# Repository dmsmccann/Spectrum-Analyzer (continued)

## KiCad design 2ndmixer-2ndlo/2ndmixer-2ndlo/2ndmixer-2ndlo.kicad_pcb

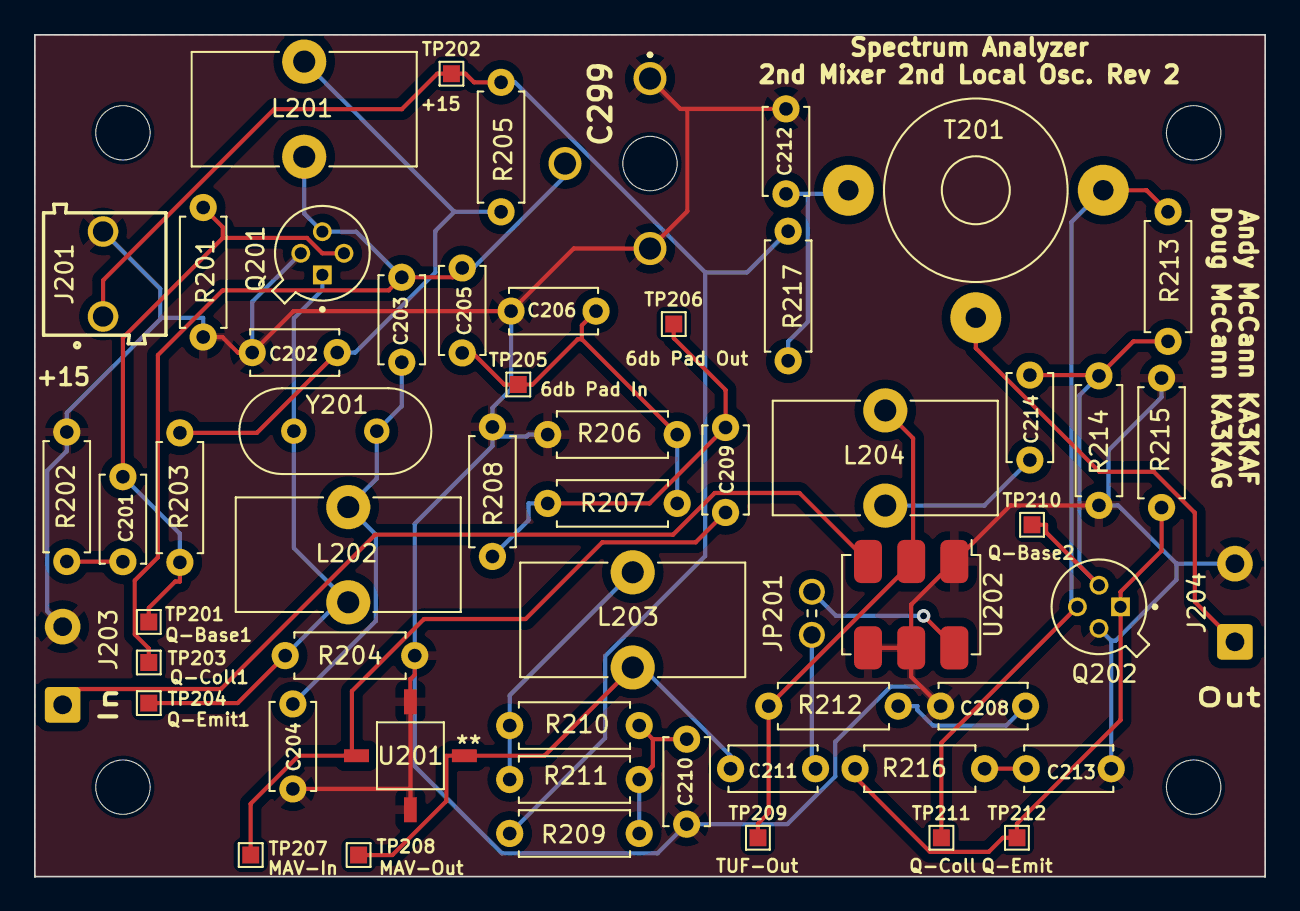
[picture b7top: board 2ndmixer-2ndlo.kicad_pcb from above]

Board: 2 copper layers, 72.4 x 49.5 mm, 61 parts (0 on the bottom side), 26 nets.

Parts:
C201, C202: 470p; C_Disc_D5.0mm_W2.5mm_P5.00mm
C203, C204: 33p; C_Disc_D5.0mm_W2.5mm_P5.00mm
C205: 15p; C_Disc_D5.0mm_W2.5mm_P5.00mm
C206: 82p; C_Disc_D5.0mm_W2.5mm_P5.00mm
C208: 120p; C_Disc_D5.0mm_W2.5mm_P5.00mm
C209, C210, C211: .01u; C_Disc_D5.0mm_W2.5mm_P5.00mm
C212, C213, C214: .1u; C_Disc_D5.0mm_W2.5mm_P5.00mm
C299: 12p-60p; BFC280831659
H201, H202, H203, H204: MountingHole; MountingHole_3.2mm_M3
J201: Conn_01x02; 691103110002
J203: 110 MHz In; SolderWire-0.5sqmm_1x02_P4.6mm_D0.9mm_OD2.1mm
J204: 2nd IF Out; SolderWire-0.5sqmm_1x02_P4.6mm_D0.9mm_OD2.1mm
JP201: 5025; KEYSTONE_5025
L201: 40n; L_Toroid_Vertical_L13.0mm_W6.5mm_P5.60mm
L202: 420n; L_Toroid_Vertical_L13.0mm_W6.5mm_P5.60mm
L203, L204: 1u; L_Toroid_Vertical_L13.0mm_W6.5mm_P5.60mm
Q201, Q202: 2N5179; TO127P584H533-4N
R201, R213: 2k; R_Axial_DIN0207_L6.3mm_D2.5mm_P7.62mm_Horizontal
R202: 39; R_Axial_DIN0207_L6.3mm_D2.5mm_P7.62mm_Horizontal
R203: 3.3k; R_Axial_DIN0207_L6.3mm_D2.5mm_P7.62mm_Horizontal
R204: 510; R_Axial_DIN0207_L6.3mm_D2.5mm_P7.62mm_Horizontal
R205: 100; R_Axial_DIN0207_L6.3mm_D2.5mm_P7.62mm_Horizontal
R206, R208: 150; R_Axial_DIN0207_L6.3mm_D2.5mm_P7.62mm_Horizontal
R207: 36; R_Axial_DIN0207_L6.3mm_D2.5mm_P7.62mm_Horizontal
R209: 47; R_Axial_DIN0207_L6.3mm_D2.5mm_P7.62mm_Horizontal
R210, R211: 220; R_Axial_DIN0207_L6.3mm_D2.5mm_P7.62mm_Horizontal
R212: 51; R_Axial_DIN0207_L6.3mm_D2.5mm_P7.62mm_Horizontal
R214: 390; R_Axial_DIN0207_L6.3mm_D2.5mm_P7.62mm_Horizontal
R215, R217: 27; R_Axial_DIN0207_L6.3mm_D2.5mm_P7.62mm_Horizontal
R216: 5.1; R_Axial_DIN0207_L6.3mm_D2.5mm_P7.62mm_Horizontal
T201: Bifilar_Transformer; Autotransformer_Toroid_1Tap_Horizontal_D10.5mm_Amidon-T37
TP201: Q-Base1; TestPoint_Pad_1.0x1.0mm
TP202: +15; TestPoint_Pad_1.0x1.0mm
TP203: Q-Coll1; TestPoint_Pad_1.0x1.0mm
TP204: Q-Emit1; TestPoint_Pad_1.0x1.0mm
TP205: 6db Pad In; TestPoint_Pad_1.0x1.0mm
TP206: 6db Pad Out; TestPoint_Pad_1.0x1.0mm
TP207: MAV-In; TestPoint_Pad_1.0x1.0mm
TP208: MAV-Out; TestPoint_Pad_1.0x1.0mm
TP209: ADE-Out; TestPoint_Pad_1.0x1.0mm
TP210: Q-Base2; TestPoint_Pad_1.0x1.0mm
TP211: Q-Coll2; TestPoint_Pad_1.0x1.0mm
TP212: Q-Emit2; TestPoint_Pad_1.0x1.0mm
U201: MAV-11; MAV-11BSM&plus_
U202: ADE-1HW+; Mini-Circuits_CD636_H4.11mm
Y201: 100MHz; Crystal_HC49-U_Vertical

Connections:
/+15: J201.1, R205.1, R209.1, R217.1, TP202.1
GND: C202.2, C204.2, C206.2, C208.2, C210.2, C212.1, C213.1, C299.1 (R_1), C299.3 (R_2), J201.2, J203.2 (Ext), J204.2 (Ext), Q201.4 (SHIELD), Q202.4 (SHIELD), R201.2, R202.2, R204.2, R206.2, R208.2, R214.2, R215.2, U201.2 (GND), U201.4 (GND), U202.1 (GND), U202.4 (GND), U202.5 (GND)
unnamed: C201.1, Q201.2, R201.1, R203.2, TP201.1
unnamed: C201.2, R202.1
unnamed: C202.1, L201.1, R203.1, R205.2
unnamed: C203.2, C204.1, L202.1, Y201.2
unnamed: C205.2, C206.1, R206.1, R207.1, TP205.1
unnamed: C208.1, R212.2
unnamed: C209.1, R207.2, R208.1, TP206.1
unnamed: C210.1, R209.2, R210.1, R211.1
unnamed: C211.2, JP201.1
unnamed: C212.2, R217.2, T201.1
unnamed: C213.2, R216.2
unnamed: C214.1, L204.2
unnamed: C214.2, Q202.2, R213.2, R214.1, TP210.1
unnamed: C203.1, C205.1, C299.2 (S), L201.2, Q201.3, TP203.1
unnamed: J203.1 (In), U202.3 (RF)
unnamed: J204.1 (In), T201.2
unnamed: L202.2, Q201.1, R204.1, TP204.1, Y201.1
unnamed: L203.1, R210.2, R211.2
unnamed: Q202.1, R215.1, R216.1, TP212.1
unnamed: Q202.3, R213.1, T201.3, TP211.1
unnamed: C209.2, TP207.1, U201.1 (RF_In)
unnamed: C211.1, L203.2, TP208.1, U201.3 (RF_Out)
unnamed: L204.1, R212.1, TP209.1, U202.2 (IF)
unnamed: JP201.2, U202.6 (LO)

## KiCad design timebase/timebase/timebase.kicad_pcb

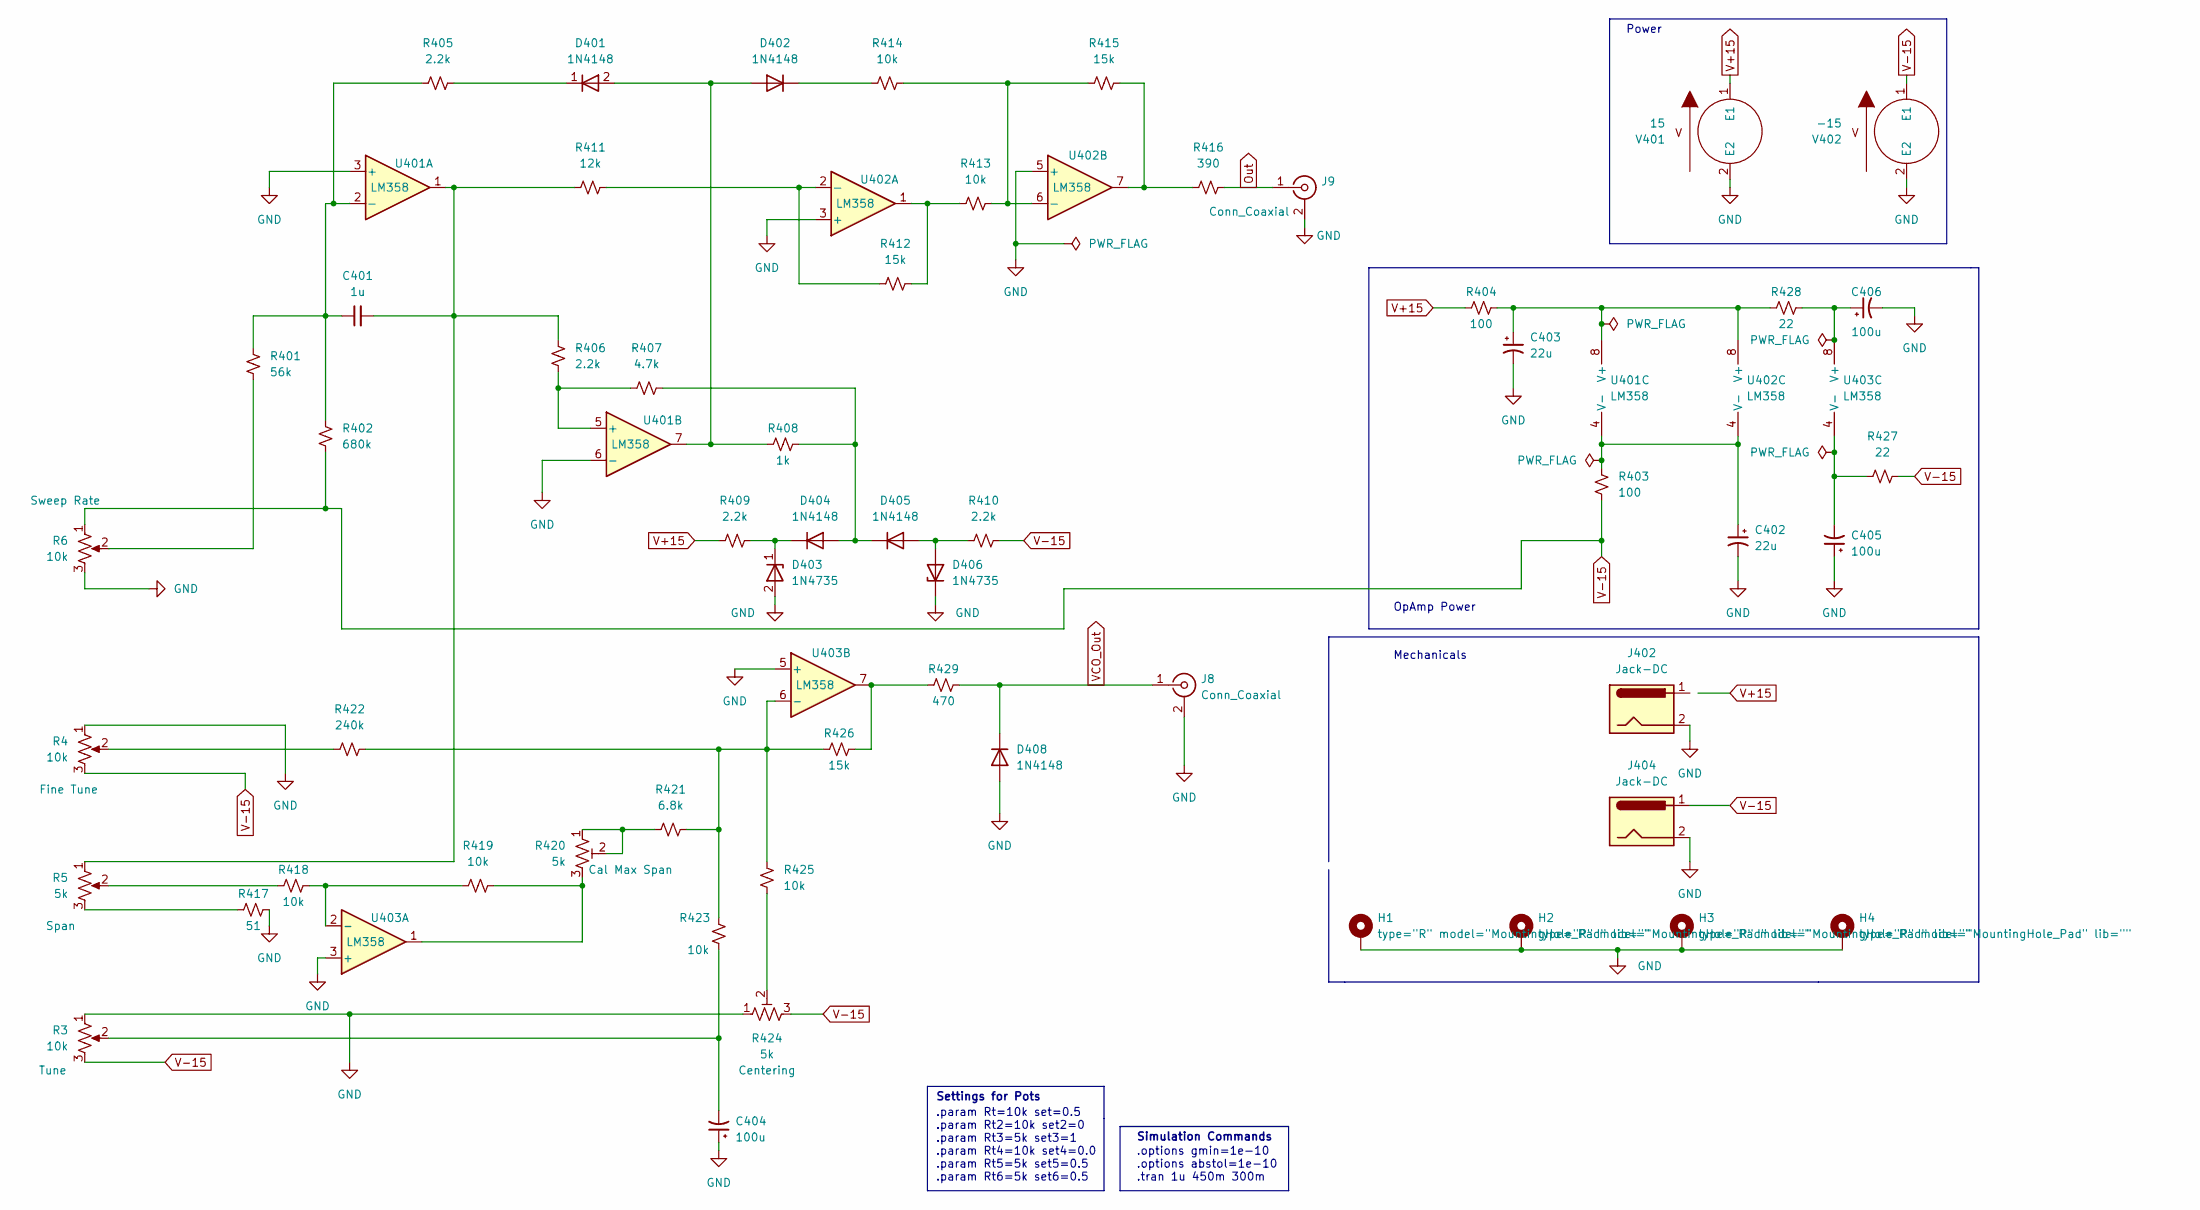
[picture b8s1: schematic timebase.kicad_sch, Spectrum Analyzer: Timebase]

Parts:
C401: 1u; C_Disc_D5.0mm_W2.5mm_P5.00mm
C402, C403: 22u; CP_Radial_D8.0mm_P3.50mm
C404, C405, C406: 100u; CP_Radial_D8.0mm_P3.50mm
D401, D402, D404, D405, D408: 1N4148; D_DO-35_SOD27_P7.62mm_Horizontal
D403, D406: 1N4735; D_DO-35_SOD27_P7.62mm_Horizontal
H1, H2, H3, H4: type="R" model="MountingHole_Pad" lib=""; MountingHole_3.2mm_M3
J8, J9: Conn_Coaxial; MOLEX_73391-0060
J402, J404: Jack-DC; 691137710002
R3, R4, R6: 10k; SolderWire-0.25sqmm_1x03_P4.2mm_D0.65mm_OD1.7mm
R5: 5k; SolderWire-0.25sqmm_1x03_P4.2mm_D0.65mm_OD1.7mm
R401: 56k; R_Axial_DIN0207_L6.3mm_D2.5mm_P7.62mm_Horizontal
R402: 680k; R_Axial_DIN0207_L6.3mm_D2.5mm_P7.62mm_Horizontal
R403, R404: 100; R_Axial_DIN0207_L6.3mm_D2.5mm_P7.62mm_Horizontal
R405, R406, R409, R410: 2.2k; R_Axial_DIN0207_L6.3mm_D2.5mm_P7.62mm_Horizontal
R407: 4.7k; R_Axial_DIN0207_L6.3mm_D2.5mm_P7.62mm_Horizontal
R408: 1k; R_Axial_DIN0207_L6.3mm_D2.5mm_P7.62mm_Horizontal
R411: 12k; R_Axial_DIN0207_L6.3mm_D2.5mm_P7.62mm_Horizontal
R412, R415, R426: 15k; R_Axial_DIN0207_L6.3mm_D2.5mm_P7.62mm_Horizontal
R413, R414, R418, R419, R423, R425: 10k; R_Axial_DIN0207_L6.3mm_D2.5mm_P7.62mm_Horizontal
R416: 390; R_Axial_DIN0207_L6.3mm_D2.5mm_P7.62mm_Horizontal
R417: 51; R_Axial_DIN0207_L6.3mm_D2.5mm_P7.62mm_Horizontal
R420, R424: 5k; Potentiometer_Bourns_3296W_Vertical
R421: 6.8k; R_Axial_DIN0207_L6.3mm_D2.5mm_P7.62mm_Horizontal
R422: 240k; R_Axial_DIN0207_L6.3mm_D2.5mm_P7.62mm_Horizontal
R427, R428: 22; R_Axial_DIN0207_L6.3mm_D2.5mm_P7.62mm_Horizontal
R429: 470; R_Axial_DIN0207_L6.3mm_D2.5mm_P7.62mm_Horizontal
U401, U402, U403: LM358; DIP794W45P254L959H508Q8
V401: 15; CUI_PJ-009A
V402: -15; CUI_PJ-009A

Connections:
GND: C402.2, C403.2, C404.1, C405.1, C406.2, D403.2 (A), D406.1 (K), D408.2 (A), H1.1, H2.1, H3.1, H4.1, J8.2 (Ext), J9.2 (Ext), J402.2, J404.2, R3.1, R4.1, R6.3, R417.2, R424.1, U401.3 (+), U401.6 (-), U402.3 (+), U402.5 (+), U403.3 (+), U403.5 (+), V401.2 (E2), V402.2 (E2)
unnamed: C403.1, R404.2, R428.1, U401.8 (V+), U402.8 (V+)
unnamed: C402.1, R403.1, U401.4 (V-), U402.4 (V-)
unnamed: C406.1, R428.2, U403.8 (V+)
unnamed: C405.2, R427.1, U403.4 (V-)
unnamed: C401.2, R5.1, R406.1, R411.1, U401.1
unnamed: C404.2, R3.2, R423.2
unnamed: D401.2 (A), D402.2 (A), R408.1, U401.7
unnamed: D401.1 (K), R405.2
unnamed: D402.1 (K), R414.1
unnamed: D403.1 (K), D404.1 (K), R409.2
unnamed: D404.2 (A), D405.1 (K), R407.2, R408.2
unnamed: D405.2 (A), D406.2 (A), R410.1
unnamed: R4.2, R422.1
unnamed: R6.2, R401.2
unnamed: R412.2, R413.1, U402.1
unnamed: R415.2, R416.1, U402.7
unnamed: R5.3, R417.1
unnamed: R5.2, R418.1
unnamed: R419.2, R420.3, U403.1
unnamed: R420.1, R420.2, R421.1
unnamed: R424.2, R425.2
unnamed: R426.2, R429.1, U403.7
unnamed: C401.1, R401.1, R402.1, R405.1, U401.2 (-)
unnamed: R406.2, R407.1, U401.5 (+)
unnamed: R411.2, R412.1, U402.2 (-)
unnamed: R413.2, R414.2, R415.1, U402.6 (-)
unnamed: R418.2, R419.1, U403.2 (-)
unnamed: R421.2, R422.2, R423.1, R425.1, R426.1, U403.6 (-)
Out: J9.1 (In), R416.2
V+15: R404.1, R409.1, V401.1 (E1)
V-15: J404.1, R3.3, R4.3, R6.1, R402.2, R403.2, R410.2, R424.3, R427.2, V402.1 (E1)
VCO_Out: D408.1 (K), J8.1 (In), R429.2

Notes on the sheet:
Mechanicals
OpAmp Power
Settings for Pots
Simulation Commands
.param Rt=10k set=0.5 .param Rt2=10k set2=0 .param Rt3=5k set3=1 .param Rt4=10k set4=0.0 .param Rt5=5k set5=0.5 .param Rt6=5k set6=0.5
Power
.options gmin=1e-10 .options abstol=1e-10 .tran 1u 450m 300m

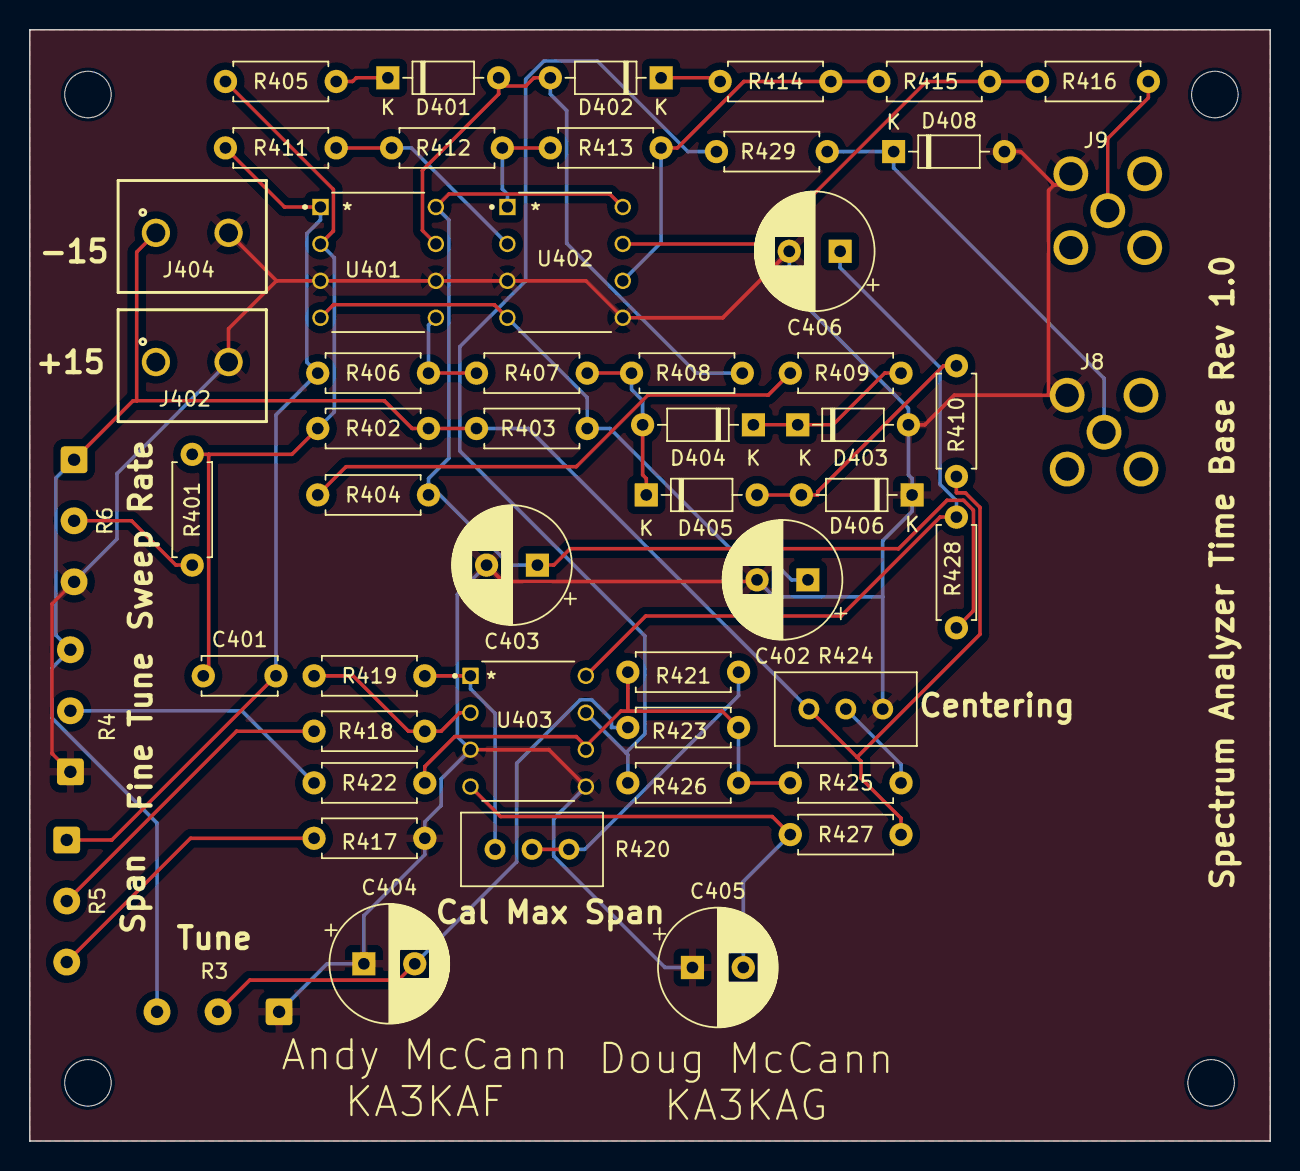
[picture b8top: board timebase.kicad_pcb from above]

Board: 2 copper layers, 85.3 x 76.5 mm, 57 parts (0 on the bottom side), 33 nets.

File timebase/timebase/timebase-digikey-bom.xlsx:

Index | Manufacturer Part Number | Manufacturer Name | Description | Attrition % | Requested Quantity 1 | Pack Quantity 1 | Pack Type 1 | Digi-Key Part Number 1 | Unit Price 1 | Extended Price 1 | Minimum Order Quantity 1 | Customer Reference
1 | CK06BX105K | KEMET | CAP CER 1UF 50V BX RADIAL |  | 1 | 1 | Bag | 1001-2031-ND | 4.91000 | $4.91 | 1 | C401
2 | LM358P | Texas Instruments | IC OPAMP GP 2 CIRCUIT 8DIP |  | 3 | 3 | Tube | 296-1395-5-ND | 0.49000 | $1.47 | 1 | U401, 402, 403
3 | 1N4735A | onsemi | DIODE ZENER 6.2V 1W DO41 |  | 2 | 2 | Bulk | 1N4735AFS-ND | 0.30000 | $0.60 | 1 | D403, 406
4 | CFR-25JT-52-390R | YAGEO | RES 390 OHM 5% 1/4W AXIAL |  | 1 | 1 | Cut Tape (CT) | 13-CFR-25JT-52-390RCT-ND | 0.10000 | $0.10 | 1 | R416
5 | CFR-25JB-52-12K | YAGEO | RES 12K OHM 5% 1/4W AXIAL |  | 1 | 1 | Bulk | 12KQBK-ND | 0.10000 | $0.10 | 1 | R411
6 | CFR-25JB-52-15K | YAGEO | RES 15K OHM 5% 1/4W AXIAL |  | 3 | 3 | Bulk | 15KQBK-ND | 0.10000 | $0.30 | 1 | R412, 415, 426
7 | CFR-25JB-52-22R | YAGEO | RES 22 OHM 5% 1/4W AXIAL |  | 2 | 2 | Bulk | 22QBK-ND | 0.10000 | $0.20 | 1 | R427, R428
8 | 3296W-1-502RLF | Bourns Inc. | TRIMMER 5K OHM 0.5W PC PIN TOP |  | 2 | 2 | Cut Tape (CT) | 3296W-1-502RLFCT-ND | 3.78000 | $7.56 | 1 | R420, 424
9 | CFR-25JB-52-56K | YAGEO | RES 56K OHM 5% 1/4W AXIAL |  | 1 | 1 | Bulk | 56KQBK-ND | 0.10000 | $0.10 | 1 | R401
10 | CFR-25JB-52-240K | YAGEO | RES 240K OHM 5% 1/4W AXIAL |  | 25 | 25 | Bulk | 240KQBK-ND | 0.04680 | $1.17 | 1 | R422
11 | 691137710002 | Würth Elektronik | TERM BLK 2POS SIDE ENTRY 5MM PCB |  | 2 | 2 | Box | 732-10955-ND | 0.41000 | $0.82 | 1 | J402, J404
12 | 226CKH050M | Cornell Dubilier / Illinois Capacitor | CAP ALUM 22UF 20% 50V RADIAL |  | 1 | 1 | Bulk | 1572-1383-ND | 0.26000 | $0.26 | 1 | C402, 403
13 | 107CKE025MEM | Cornell Dubilier / Illinois Capacitor | CAP ALUM 100UF 20% 25V RADIAL |  | 1 | 1 | Bulk | 1572-1039-ND | 0.38000 | $0.38 | 1 | C404, 405, 406
14 | 1N4148 | SMC Diode Solutions | DIODE GEN PURP 75V 300MA DO35 |  | 1 | 1 | Cut Tape (CT) | 1655-1N4148CT-ND | 0.13000 | $0.13 | 1 | D401, 402, 404, 405, 408
15 | 0733910060 | Molex | CONN SMA RCPT STR 50 OHM PCB |  | 2 | 2 | Tray | WM5543-ND | 3.88000 | $7.76 | 1 | J402, 404
16 | 502-0308 | NTE Electronics, Inc | POT 10K OHM 1/5W LINEAR |  | 3 | 3 | Bag | 2368-502-0308-ND | 1.44000 | $4.32 | 1 | R3, R4, R6
17 | 502-0305 | NTE Electronics, Inc | POT 5K OHM 1/5W LINEAR |  | 1 | 1 | Bag | 2368-502-0305-ND | 1.08000 | $1.08 | 1 | R5
18 | CFR-25JT-52-680K | YAGEO | RES 680K OHM 5% 1/4W AXIAL |  | 1 | 1 | Cut Tape (CT) | 13-CFR-25JT-52-680KCT-ND | 0.10000 | $0.10 | 1 | R402
19 | CFR-25JB-52-100R | YAGEO | RES 100 OHM 5% 1/4W AXIAL |  | 2 | 2 | Bulk | 100QBK-ND | 0.10000 | $0.20 | 1 | R403, 404
20 | CFR-25JB-52-2K2 | YAGEO | RES 2.2K OHM 5% 1/4W AXIAL |  | 4 | 4 | Bulk | 2.2KQBK-ND | 0.10000 | $0.40 | 1 | R405, 406, 409, 410
21 | CFR-25JB-52-4K7 | YAGEO | RES 4.7K OHM 5% 1/4W AXIAL |  | 1 | 1 | Bulk | 4.7KQBK-ND | 0.10000 | $0.10 | 1 | R407
22 | CFR-25JB-52-1K | YAGEO | RES 1K OHM 5% 1/4W AXIAL |  | 1 | 1 | Bulk | 1.0KQBK-ND | 0.10000 | $0.10 | 1 | R408
23 | CFR-25JB-52-10K | YAGEO | RES 10K OHM 5% 1/4W AXIAL |  | 6 | 6 | Bulk | 10KQBK-ND | 0.10000 | $0.60 | 1 | R413, 414, 418, 419, 423, 425
24 | CFR-25JB-52-51R | YAGEO | RES 51 OHM 5% 1/4W AXIAL |  | 1 | 1 | Bulk | 51QBK-ND | 0.10000 | $0.10 | 1 | R417
25 | CFR-25JB-52-6K8 | YAGEO | RES 6.8K OHM 5% 1/4W AXIAL |  | 1 | 1 | Bulk | 6.8KQBK-ND | 0.10000 | $0.10 | 1 | R421
26 | CFR-25JB-52-470R | YAGEO | RES 470 OHM 5% 1/4W AXIAL |  | 1 | 1 | Bulk | 470QBK-ND | 0.10000 | $0.10 | 1 | R429

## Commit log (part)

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2022-05-09 kicad timebase board
2022-05-09 Schematic update
    Improved ability to run sim
2022-05-09 fixing master and main
2022-05-29 timebase pcb routed
2022-05-29 adding hayward references
2022-05-29 added minor change to README.md
2022-05-30 IF and log amp added
2022-05-30 Improvements to overall schematics
2022-05-30 adding references
2022-05-30 adding archives
2022-05-30 additional chamges
2022-05-30 fixing schematics
2022-05-30 yet another repair
2022-05-30 catching up
2022-05-30 backups
2022-05-30 test deletion
2022-05-30 added the in the right place of the README.md file
2022-05-31 Resolution filters ltspice and kicad files
2022-06-01 corrected 10V power supply and component values in IF filter
2022-06-01 updates to if amp section
2022-06-01 Reduced size of timebase pcb
2022-06-01 fixed broken wire by R319
2022-06-01 added missing wire in 10V regulator
2022-06-05 added schematic for dual polarity supply
2022-06-05 reorganized folders
2022-06-05 removed folder power-supply
2022-06-05 changed schematic sheet notes
2022-06-05 added power flags, ERC checks pass
2022-06-06 updated schematic -- cannot pass erc
2022-06-07 updates to 15 v supply and if log amp boards
2022-06-09 updates to the 15v-supply spice models
2022-06-12 Significant changes to timebase spice, 15v supply and resolution-filters
2022-06-15 Changes to 15v supply including symbol annotation, BOM, footprints, and folder reorg
2022-06-15 more improvements to 15v-supply
2022-06-16 15v-supply routed and poured
2022-06-18 updated spice library path, edited silkscreen and schematic for rev0.0
2022-06-18 if and log amp routing and 3d model
2022-06-18 remove timebase.raw
2022-06-19 Improvements to if and log amp
2022-06-19 If and Log Amp spice improvements
2022-06-19 changed 220p cap back to variable
2022-06-19 cleanup of W7ZOI Spectrum Analyzer project files
2022-06-19 further improvements on folder organization
2022-06-19 add README.md
2022-06-19 improvements to hierarchical schematic
2022-06-19 qst QST_Aug_1998 added to lit folder
2022-06-21 updates to 15v supply and if and log amp boards so boards can be sent to fab
2022-06-23 resolution filter with crystal filter added
2022-07-10 resolution-filters update
2022-07-16 15v-supply changes
2022-07-16 added to change log
2022-07-17 CA3140 pin 4 ground
2022-07-17 no connect on pin 1 of CA3140
2022-07-17 minor change to J305
2022-07-17 15v-supply updates
2022-07-17 15v-supply update
2022-07-18 timebase updates
2022-07-18 timebase auto save
2022-07-20 some improvements to timebase and if log amp
2022-07-20 Rev 1 Changes for if and log amp
2022-07-20 if log amp change log update
2022-07-20 minor changes to log amp board
2022-07-23 further improvements to if-log amp
2022-07-24 two two-tone-test added
2022-07-25 revised if and log amp schematic and board
2022-07-29 resolution filters board layout
2022-07-30 resolution filter board layout
2022-07-31 updates to if log amp and resolution filter boards
2022-07-31 fix transformer issue
2022-07-31 resolution filter improvement and bom
2022-08-05 2ndmixer-2ndlo
2022-08-06 minor fixes to 2ndmixer-2ndlo
2022-08-06 made 4 changes to schematic
2022-08-06 minor changes to schematic
2022-08-08 2ndmixer-2ndlo layout
2022-08-14 various updates
2022-08-15 Add amp to if-and-log-amp
2022-08-15 2db-div schematic added
2022-08-15 add annotations to 2db-div schematic
2022-08-20 improved if and log amp and second lo/mixer
2022-08-20 added some test points
2022-08-20 rm autosaved files
2022-08-21 updates to 2ndmixer-2ndlo
2022-08-21 vco 1st mixer board
2022-08-21 2ndmixer-2ndlo bom and corrections
2022-08-21 minor fix to 2ndmixer-2ndlo
2022-08-22 2db-div layout
2022-08-22 BOM for 2db-div
2022-08-22 vco-1stmixer bom
2022-08-22 70mhz-lpf
2022-08-23 Hierarchical schematic updates
2022-08-24 hierarchical schematic updated to pass erc
2022-08-24 update to 15v schematic and trying new theme
2022-08-24 appearance improvements
2022-08-25 added junction at base of 2N5179
2022-08-25 2ndmixer-2ndlo pcb fix
2022-08-25 minor changes to 5 boards
2022-08-26 minor changes for spice
2022-09-03 70MHz spice model update
2022-12-11 Fix POS200 footprint and Terminal Block footprint of VCO 1st Mixer Board. Rev 1.
2022-12-27 minor edit to timebase
2022-12-27 updated paper on 110MHz filter
2022-12-27 qex 1998 article and changes to vco 1st mixer pcb
2023-01-08 Fixes to 2ndmixer-2ndlo and vco-1stmixer
2023-01-16 corrections to resolution-filters
2023-01-16 resolution-filters.kicad_pcb updated
2023-01-16 resolution-filters updates
2023-01-16 resolution-filters - one more fix
2023-01-16 resolution-filters pcb silkscreen repair
2023-01-21 spice model for resolution-filters
2023-01-22 ltspice model
2023-03-09 v7 conversion
2023-03-11 2ndmixer-2ndlo rev 1
2023-03-11 xtal.lib
2023-03-11 removing spice
2023-03-11 Fix tuf1h symbol
2023-03-11 minor changes
2023-03-12 saved error reports
2023-03-18 Update to timebase and 2lo gerbers
2023-07-08 self oscillator
2023-08-06 2nd-lo spice
2023-08-06 2nd-lo with variable resistor
2023-08-06 2nd-lo fixed
2023-08-06 2nd-lo
2023-08-06 2nd-lo oscillating
2023-08-08 2nd-lo oscillating
    add hayward original design
2023-09-04 2nd lo kanga
2023-11-19 partial 2nd lo fixes
2023-11-20 latest 2ndlo
2023-11-22 updates to 2nd lo
2023-11-30 further change to 2nd LO schematic and board
2023-12-02 Match to Kanga layout
2023-12-03 2ndmixer-2ndlo.kicad_sch change to ADE-1H
2023-12-03 remove some files
2023-12-05 first sections of tracking-generator
2023-12-05 adding +6V section of tracking-generator
2023-12-10 tracking-generator amplifier stage added
2023-12-11 updated digikey # ade-1h
2023-12-21 2nd div board tweaks
    Updated component symbols
2023-12-21 Minor updates to 2nd db board
    primarily renaming nets
2023-12-21 lt spice sim for low pass filter
2023-12-28 erc changes for hierarchical schematic
2024-01-01 updates to hierarchical schematic
2024-01-07 correction to hierarchical schematic
2024-01-07 adding 7mhz crystal oscillator
2024-01-19 7mhz xtal oscillator
2024-01-21 crystal oscillator models
2024-01-28 Added R2
2024-02-04 timebase rev 1 - fixes silkscreen
2024-02-04 updates to 2db board
2024-02-04 7mhz oscillator ltspice
2024-02-11 updates to 15v-supply
2024-02-11 resolution filter spice updates
2024-02-11 if and log amp - add version 0 pcb to directory
2024-02-11 gitignore change
2024-02-11 6-22 if and log amp schematic
2024-03-02 if log amp project file
2024-03-10 IF Log Amp V2
2024-03-10 minor edits to 15v supply
2024-03-10 2db minor changes
2024-03-10 2nd mixer minor changes
2024-03-10 footprint updates
2024-03-10 resolution filter minor changes
2024-03-10 timebase minor changes
2024-03-10 if log amp minor change
2024-03-12 if and log amp ibom
2024-03-25 Add Digikey part numbers to schematic
2024-03-25 minor 2db/div changes
2024-03-25 minor changes to multiple boards
2025-01-26 70Mhz spice models
2025-01-26 updatess to kicad v8
2025-01-26 1st mixer VCO pcb rev 2
2025-07-20 update to readme
2026-05-10 updates to 1st vco mixer to add some 3D Models
2026-05-10 minor updates
